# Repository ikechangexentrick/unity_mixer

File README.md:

# unity_mixer
2 channel, 3 input unity gain mixer

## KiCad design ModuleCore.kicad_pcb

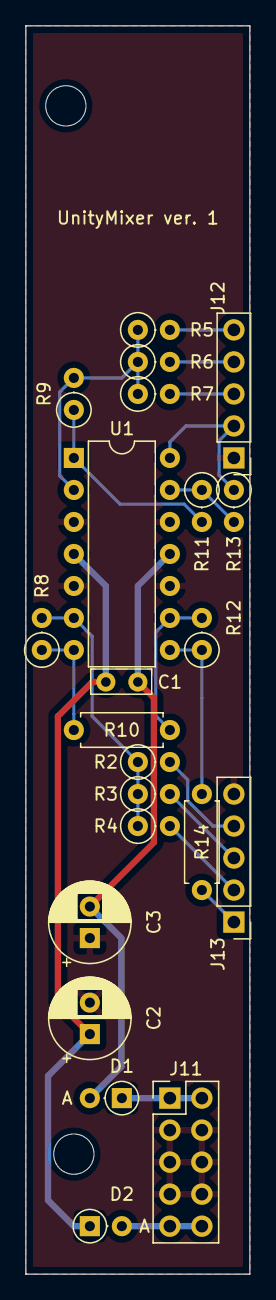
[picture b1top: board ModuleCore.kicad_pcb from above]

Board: 2 copper layers, 17.8 x 99.1 mm, 22 parts (0 on the bottom side), 20 nets.

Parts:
C1: 0.1u; C_Axial_L4.8mm_D2.0mm_P2.54mm_Horizontal
C2, C3: 100u; CP_Radial_D6.3mm_P2.50mm
D1, D2: D_Schottky; D_DO-35_SOD27_P2.54mm_Vertical_AnodeUp
J11: power_bus; PinHeader_2x05_P2.54mm_Vertical
J12: conn1; PinHeader_1x05_P2.54mm_Vertical
J13: conn2; PinHeader_1x05_P2.54mm_Vertical
R2, R3, R4, R5, R6, R7, R8, R9: 100k; R_Axial_DIN0207_L6.3mm_D2.5mm_P2.54mm_Vertical
R10: 10k; R_Axial_DIN0207_L6.3mm_D2.5mm_P7.62mm_Horizontal
R11, R12, R13: 10k; R_Axial_DIN0207_L6.3mm_D2.5mm_P2.54mm_Vertical
R14: 1k; R_Axial_DIN0207_L6.3mm_D2.5mm_P7.62mm_Horizontal
U1: TL074; DIP-14_W7.62mm

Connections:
+12V: C1.1, C2.1, D2.1, U1.4
-12V: C1.2, C3.2, D1.2, U1.11
/Core/ch1_1: J12.5, R5.2
/Core/ch1_2: J12.4, R6.2
/Core/ch1_3: J12.3, R7.2
/Core/ch1_out: J12.2, R13.1, U1.14
/Core/ch2_1: J13.4, R2.2
/Core/ch2_2: J13.3, R3.2
/Core/ch2_3: J13.2, R4.2
/Core/ch2_out: J13.1, R14.1
GND: C2.2, C3.1, J11.3, J11.4, J11.5, J11.6, J11.7, J11.8, J12.1, J13.5, U1.3, U1.5, U1.10, U1.12
unnamed: D1.1, J11.1, J11.2
unnamed: D2.2, J11.9, J11.10
unnamed: R2.1, R3.1, R4.1, R8.2, U1.6
unnamed: R5.1, R6.1, R7.1, R9.2, U1.2
unnamed: R10.1, R12.2, U1.9
unnamed: R8.1, R10.2, U1.7
unnamed: R11.1, R13.2, U1.13
unnamed: R9.1, R11.2, U1.1
unnamed: R12.1, R14.2, U1.8

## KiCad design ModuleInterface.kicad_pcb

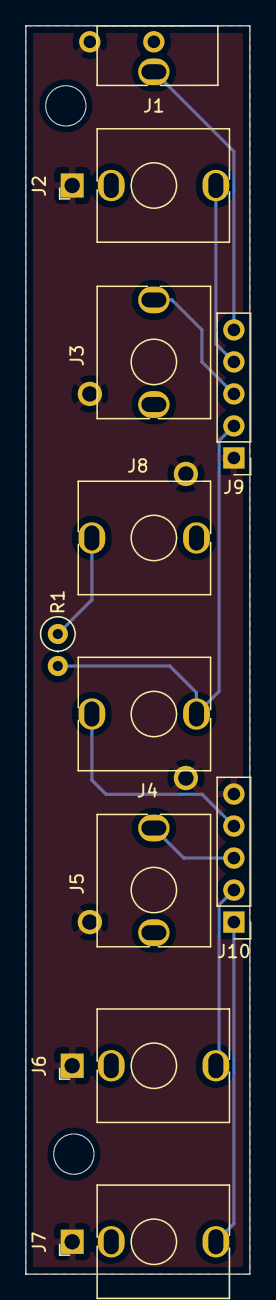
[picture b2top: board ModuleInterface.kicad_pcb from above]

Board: 2 copper layers, 17.8 x 99.1 mm, 13 parts (0 on the bottom side), 10 nets.

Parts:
1, 2: annotation_3.5mm_jack_out
J1: ch1_1; mono_jack_terminal_only_wo_TN
J2: ch1_2; mono_jack_3.5mm
J3: ch1_3; mono_jack_3.5mm_wo_GND
J4: ch2_1; mono_jack_3.5mm_wo_GND
J5: ch2_2; mono_jack_3.5mm_wo_GND
J6: ch2_3; mono_jack_3.5mm
J7: ch2_out; mono_jack_3.5mm
J8: ch1_out; mono_jack_3.5mm_wo_GND_L
J9: conn1; PinHeader_1x05_P2.54mm_Vertical
J10: conn2; PinHeader_1x05_P2.54mm_Vertical
R1: 1k; R_Axial_DIN0207_L6.3mm_D2.5mm_P2.54mm_Vertical

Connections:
/Interface/ch1_1: J1.T, J9.5
/Interface/ch1_2: J2.T, J9.4
/Interface/ch1_3: J3.T, J9.3
/Interface/ch1_out: J4.TN, J9.2, R1.2
/Interface/ch2_1: J4.T, J10.4
/Interface/ch2_2: J5.T, J10.3
/Interface/ch2_3: J6.T, J10.2
/Interface/ch2_out: J7.T, J10.1
GND: J1.S, J2.S, J3.S, J4.S, J5.S, J6.S, J7.S, J8.S, J9.1, J10.5
unnamed: J8.T, R1.1

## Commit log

2022-09-08 Unity gain mixer
